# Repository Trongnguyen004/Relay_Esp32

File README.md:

# Relay_Esp32

### #Hình ảnh

<p align="center">
  <table>
    <tr>
      <td>
        
      </td>
      <td>
        
      </td>
      <td>
        
      </td>
    </tr>
  </table>
</p>

### #Video
https://github.com/Trongnguyen004/Relay_Esp32/assets/137270832/a6e5d2e0-7b71-4601-a6b4-ad4e370f64c5

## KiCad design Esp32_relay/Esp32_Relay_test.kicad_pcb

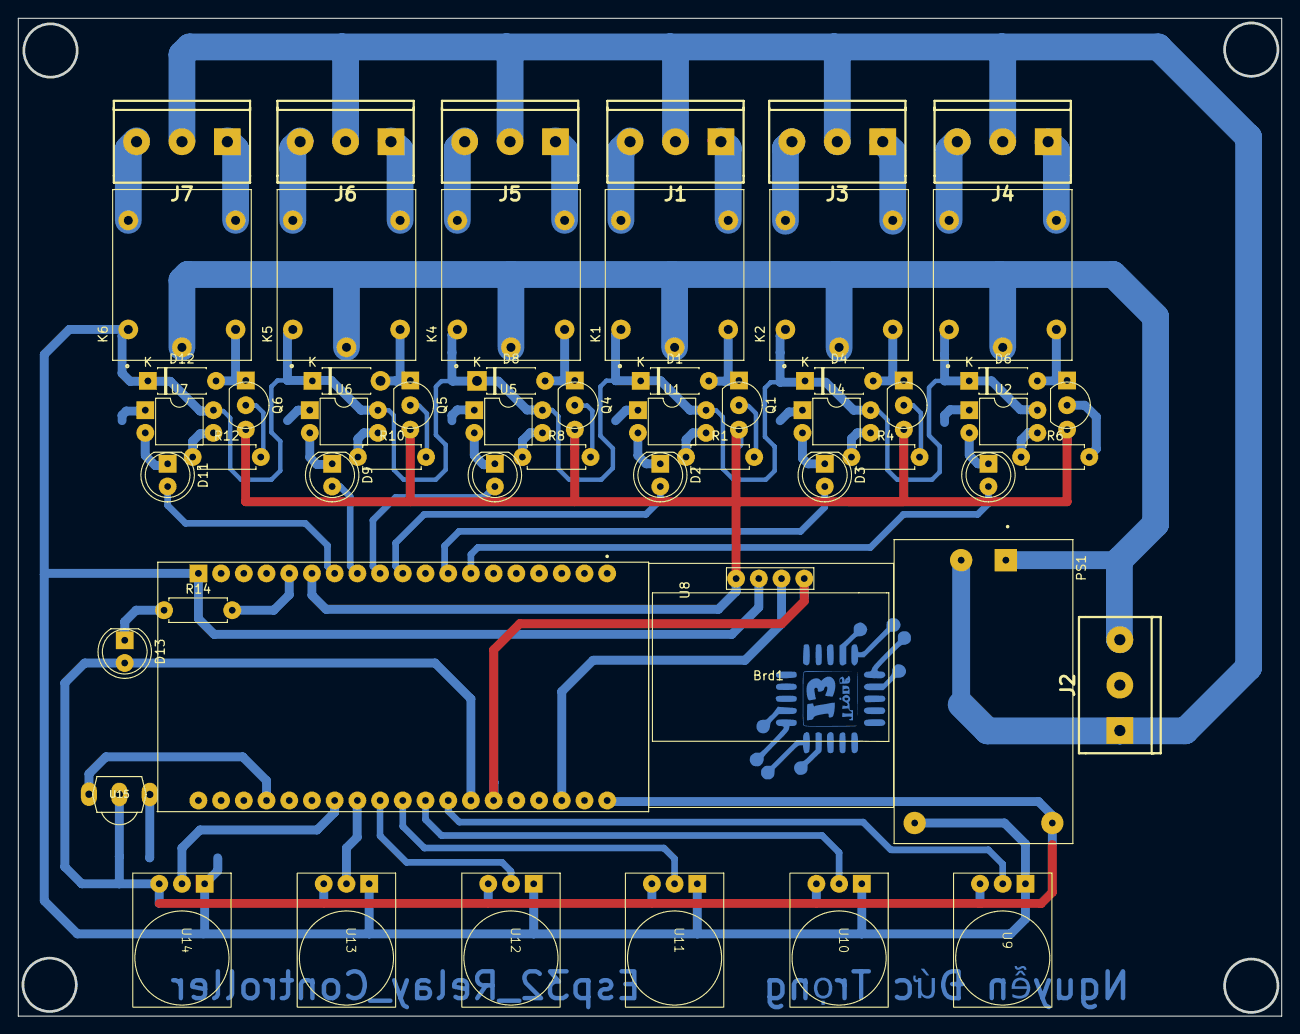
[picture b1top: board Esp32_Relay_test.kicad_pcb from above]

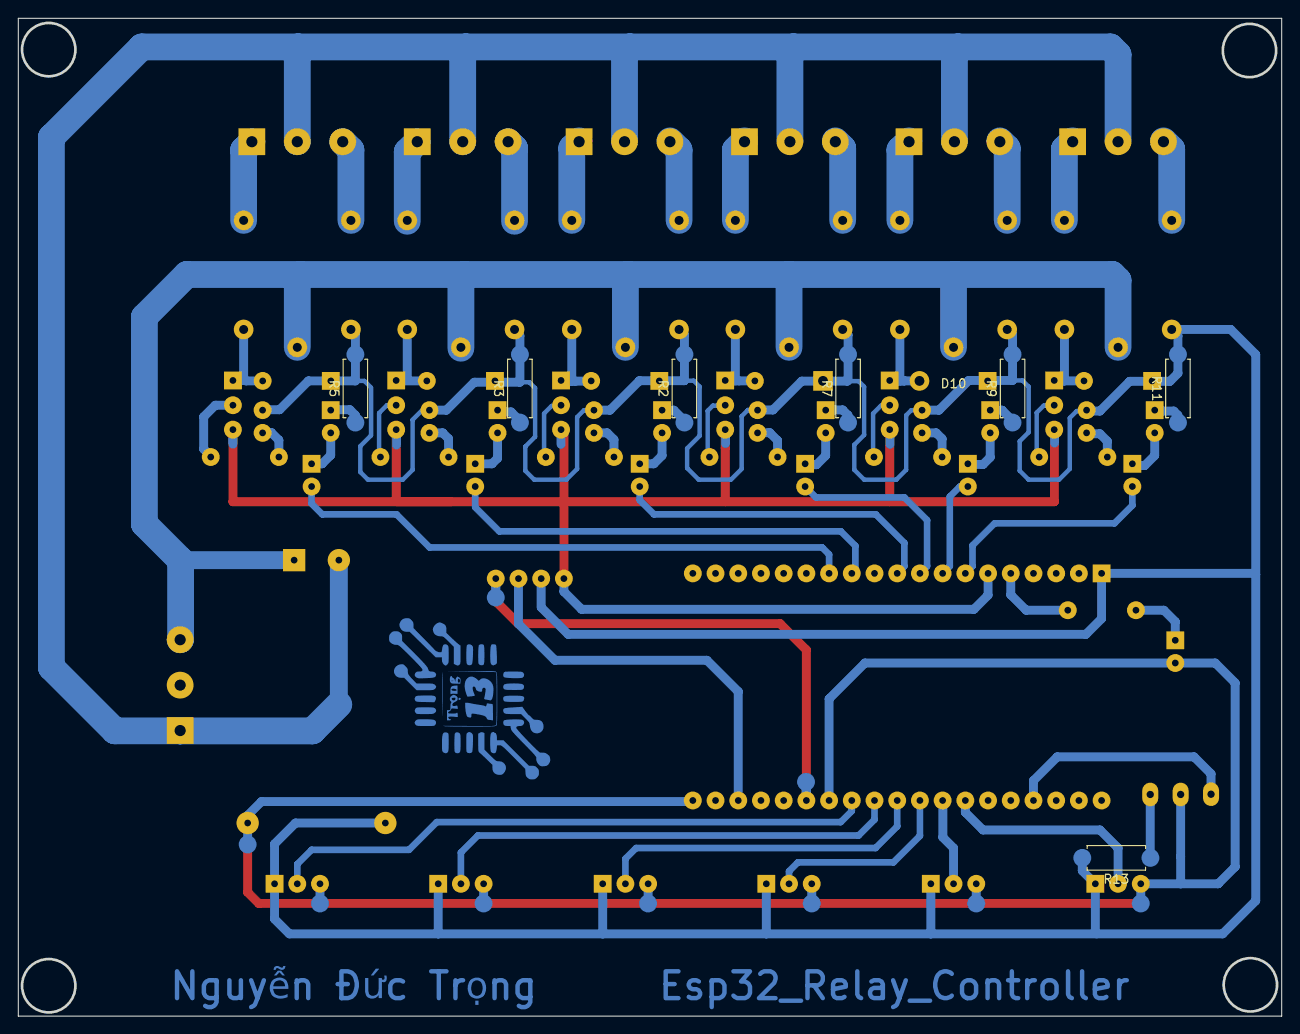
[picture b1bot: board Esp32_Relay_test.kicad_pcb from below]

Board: 2 copper layers, 141.1 x 111.4 mm, 62 parts (7 on the bottom side), 64 nets.

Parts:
Brd1: SSD1306; 128x64OLED
D1, D4, D6, D8, D10, D12: D; D_DO-41_SOD81_P7.62mm_Horizontal
D2, D3, D5, D7, D9, D11, D13: LED_D5.0mm
J1, J2, J3, J4, J5, J6, J7: Screw_Terminal_01x03; KF301-3P
K1, K2, K3, K4, K5, K6: SRD-05VDC-SL-C; RELAY_SRD-05VDC-SL-C
PS1: HLK-PM01; CONV_HLK-PM01
Q1, Q2, Q3, Q4, Q5, Q6: BC547; TO-92_Inline
R1, R4, R6, R8, R10, R12: 1k; R_Axial_DIN0207_L6.3mm_D2.5mm_P7.62mm_Horizontal
R2, R5, R7, R9, R11: 330; R_Axial_DIN0207_L6.3mm_D2.5mm_P7.62mm_Horizontal
R3, R13, R14: 100; R_Axial_DIN0207_L6.3mm_D2.5mm_P7.62mm_Horizontal
U1, U2, U4, U5, U6, U7: PC817; DIP-4_W7.62mm
U8: ESP32-DEVKITC-32D; MODULE_ESP32-DEVKITC-32D
U9, U10, U11, U12, U13, U14: TTP223
U15: TSOP1838; TSOP18XX

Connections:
+5V: Brd1.2 (VCC), D1.1 (K), D4.1 (K), D6.1 (K), D8.1 (K), D10.1 (K), D12.1 (K), K1.A1, K2.A1, K3.A1, K4.A1, K5.A1, K6.A1, PS1.4 (+VO), R2.2, R3.2, R5.2, R7.2, R9.2, R11.2, R13.2, U1.4, U2.4, U4.4, U5.4, U6.4, U7.4, U8.J2-19 (EXT_5V), U9.1 (Vcc), U10.1 (Vcc), U11.1 (Vcc), U12.1 (Vcc), U13.1 (Vcc), U14.1 (Vcc)
/1: D11.2, U8.J2-13 (IO12)
/2: D9.2, U8.J2-12 (IO14)
/3: D7.2, U8.J2-11 (IO27)
/4: D2.2, U8.J2-10 (IO26)
/5: D3.2, U8.J2-8 (IO33)
/6: D5.2, U8.J2-7 (IO32)
/B1: U8.J3-13 (IO4), U14.2 (I/O)
/B2: U8.J3-12 (IO16), U13.2 (I/O)
/B3: U8.J3-11 (IO17), U12.2 (I/O)
/B4: U8.J3-10 (IO5), U11.2 (I/O)
/B5: U8.J3-9 (IO18), U10.2 (I/O)
/B6: U8.J3-8 (IO19), U9.2 (I/O)
/IR: U8.J3-16 (IO15), U15.OUT
/SCL: Brd1.3 (SCL), U8.J3-3 (IO22)
/SDA: Brd1.4 (SDA), U8.J3-6 (IO21)
GND: Brd1.1 (GND), D13.2, PS1.3 (-VO), Q1.3 (E), Q2.3 (E), Q3.3 (E), Q4.3 (E), Q5.3 (E), Q6.3 (E), U8.J2-14 (GND1), U8.J3-1 (GND3), U8.J3-7 (GND2), U9.3 (GND), U10.3 (GND), U11.3 (GND), U12.3 (GND), U13.3 (GND), U14.3 (GND), U15.GND
GNDREF: J1.2, J2.1, J3.2, J4.2, J5.2, J6.2, J7.2, PS1.2 (AC2)
unnamed: D1.2 (A), K1.A2, Q1.1 (C)
unnamed: D2.1, U1.2
unnamed: D3.1, U4.2
unnamed: D4.2 (A), K2.A2, Q2.1 (C)
unnamed: D5.1, U2.2
unnamed: D6.2 (A), K3.A2, Q3.1 (C)
unnamed: D7.1, U5.2
unnamed: D8.2 (A), K4.A2, Q4.1 (C)
unnamed: D9.1, U6.2
unnamed: D10.2 (A), K5.A2, Q5.1 (C)
unnamed: D11.1, U7.2
unnamed: D12.2 (A), K6.A2, Q6.1 (C)
unnamed: D13.1, R14.1
unnamed: J1.1, K1.NO
unnamed: J1.3, K1.NC
unnamed: J3.1, K2.NO
unnamed: J3.3, K2.NC
unnamed: J4.1, K3.NO
unnamed: J4.3, K3.NC
unnamed: J5.1, K4.NO
unnamed: J5.3, K4.NC
unnamed: J6.1, K5.NO
unnamed: J6.3, K5.NC
unnamed: J7.1, K6.NO
unnamed: J7.3, K6.NC
unnamed: Q1.2 (B), R1.2
unnamed: Q2.2 (B), R4.2
unnamed: Q3.2 (B), R6.2
unnamed: Q4.2 (B), R8.2
unnamed: Q5.2 (B), R10.2
unnamed: Q6.2 (B), R12.2
unnamed: R1.1, U1.3
unnamed: R2.1, U1.1
unnamed: R3.1, U4.1
unnamed: R4.1, U4.3
unnamed: R5.1, U2.1
unnamed: R6.1, U2.3
unnamed: R7.1, U5.1
unnamed: R8.1, U5.3
unnamed: R9.1, U6.1
unnamed: R10.1, U6.3
unnamed: R11.1, U7.1
unnamed: R12.1, U7.3
unnamed: R14.2, U8.J2-15 (IO13)
unnamed: R13.1, U15.VCC (V+)
VAC: J2.3, K1.COM, K2.COM, K3.COM, K4.COM, K5.COM, K6.COM, PS1.1 (AC1)
